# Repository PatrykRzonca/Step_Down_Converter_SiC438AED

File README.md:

# Step_Down_Converter_SiC438AED
Educational project for high current buck converters

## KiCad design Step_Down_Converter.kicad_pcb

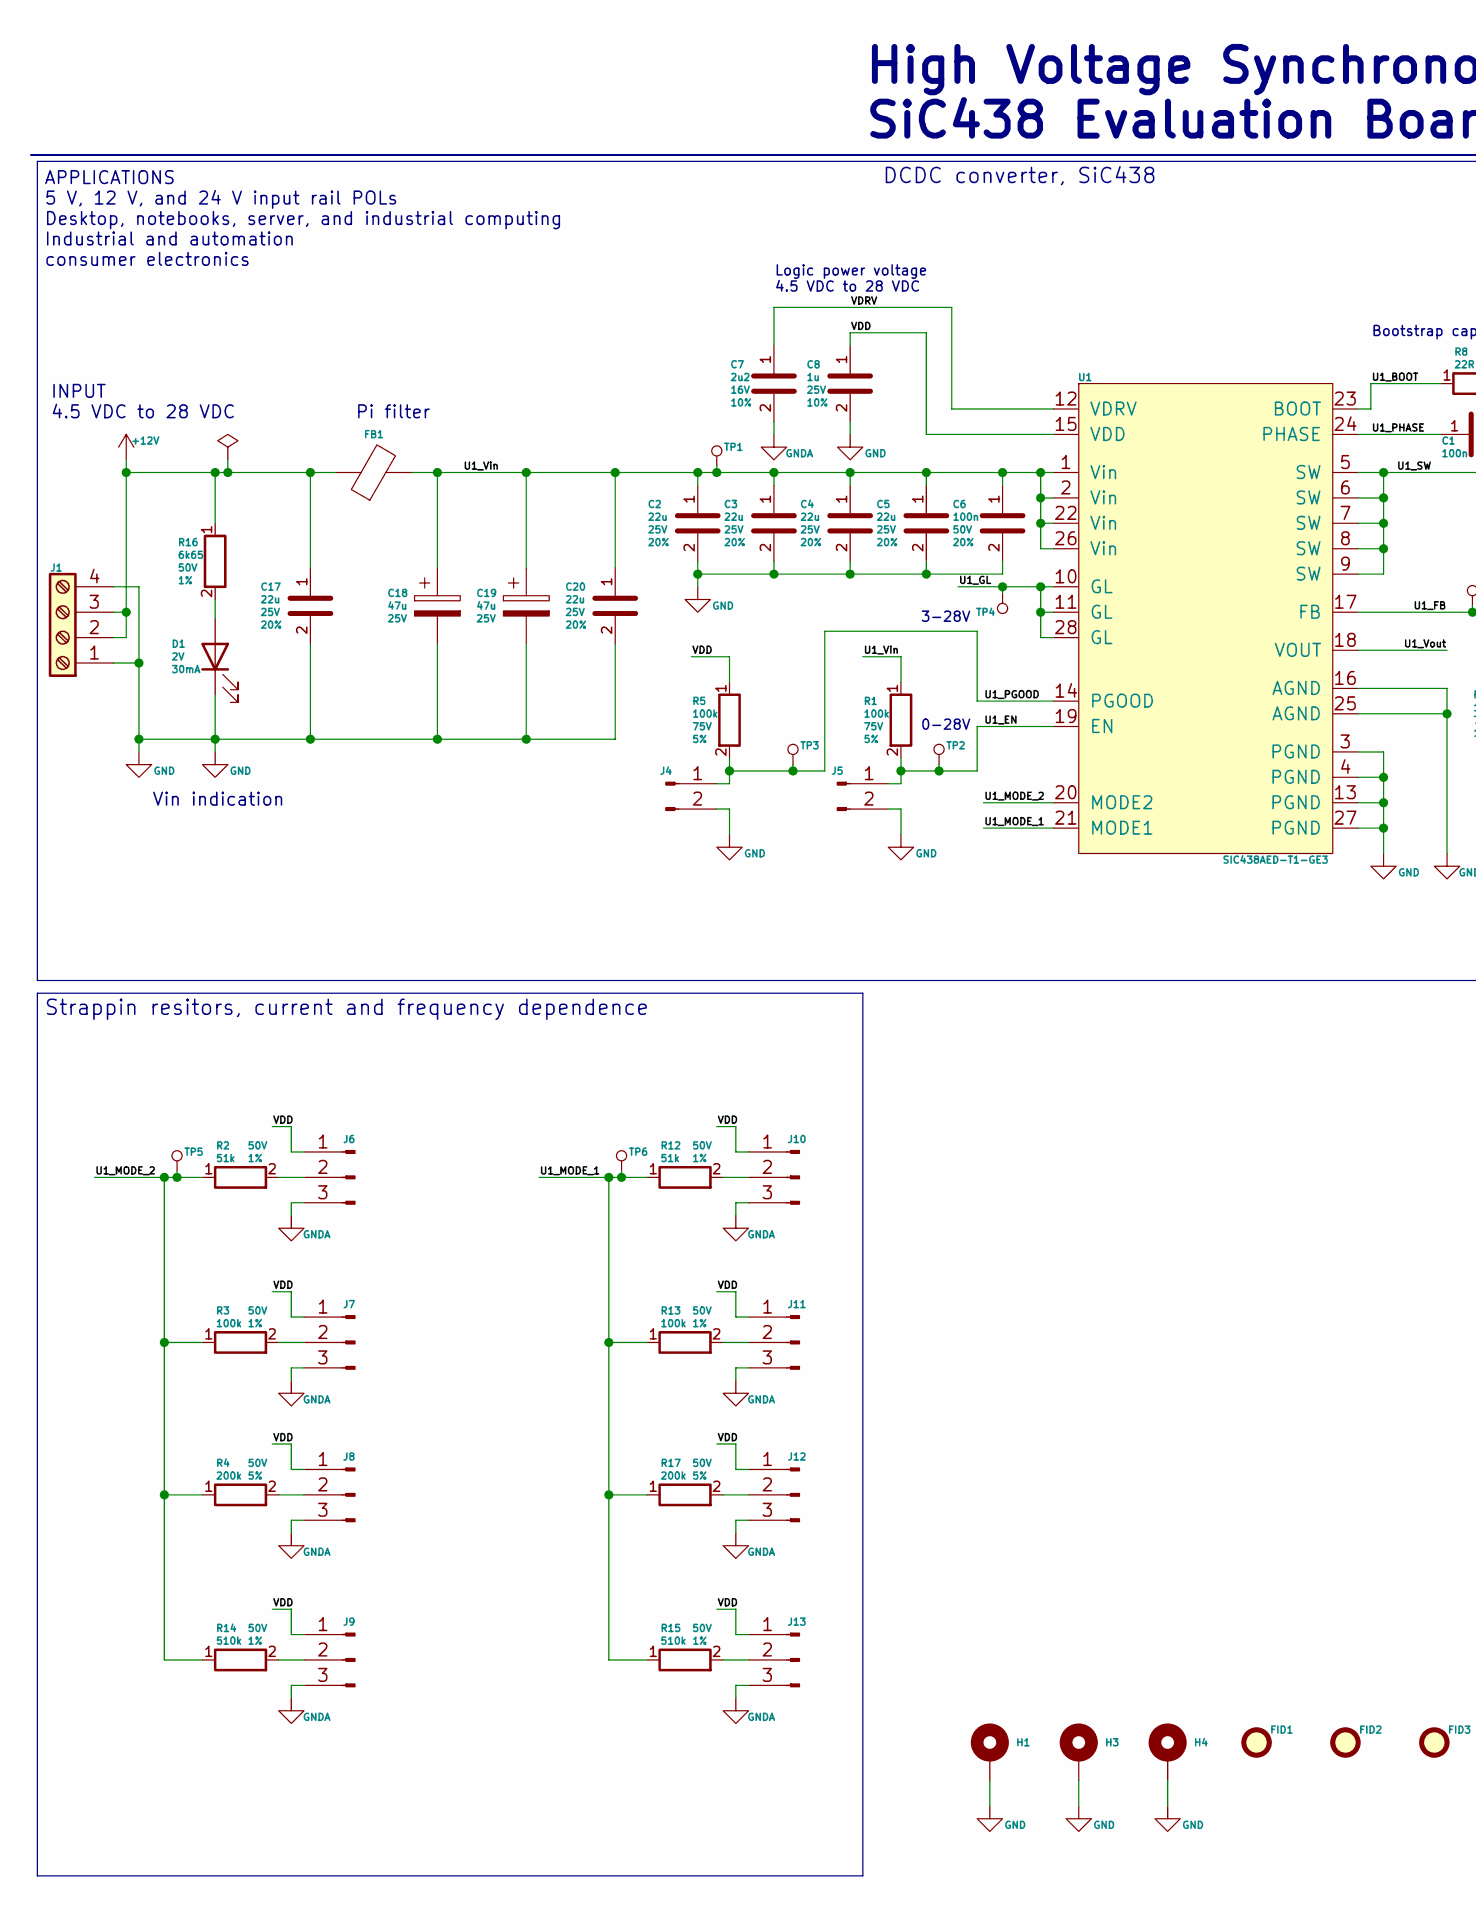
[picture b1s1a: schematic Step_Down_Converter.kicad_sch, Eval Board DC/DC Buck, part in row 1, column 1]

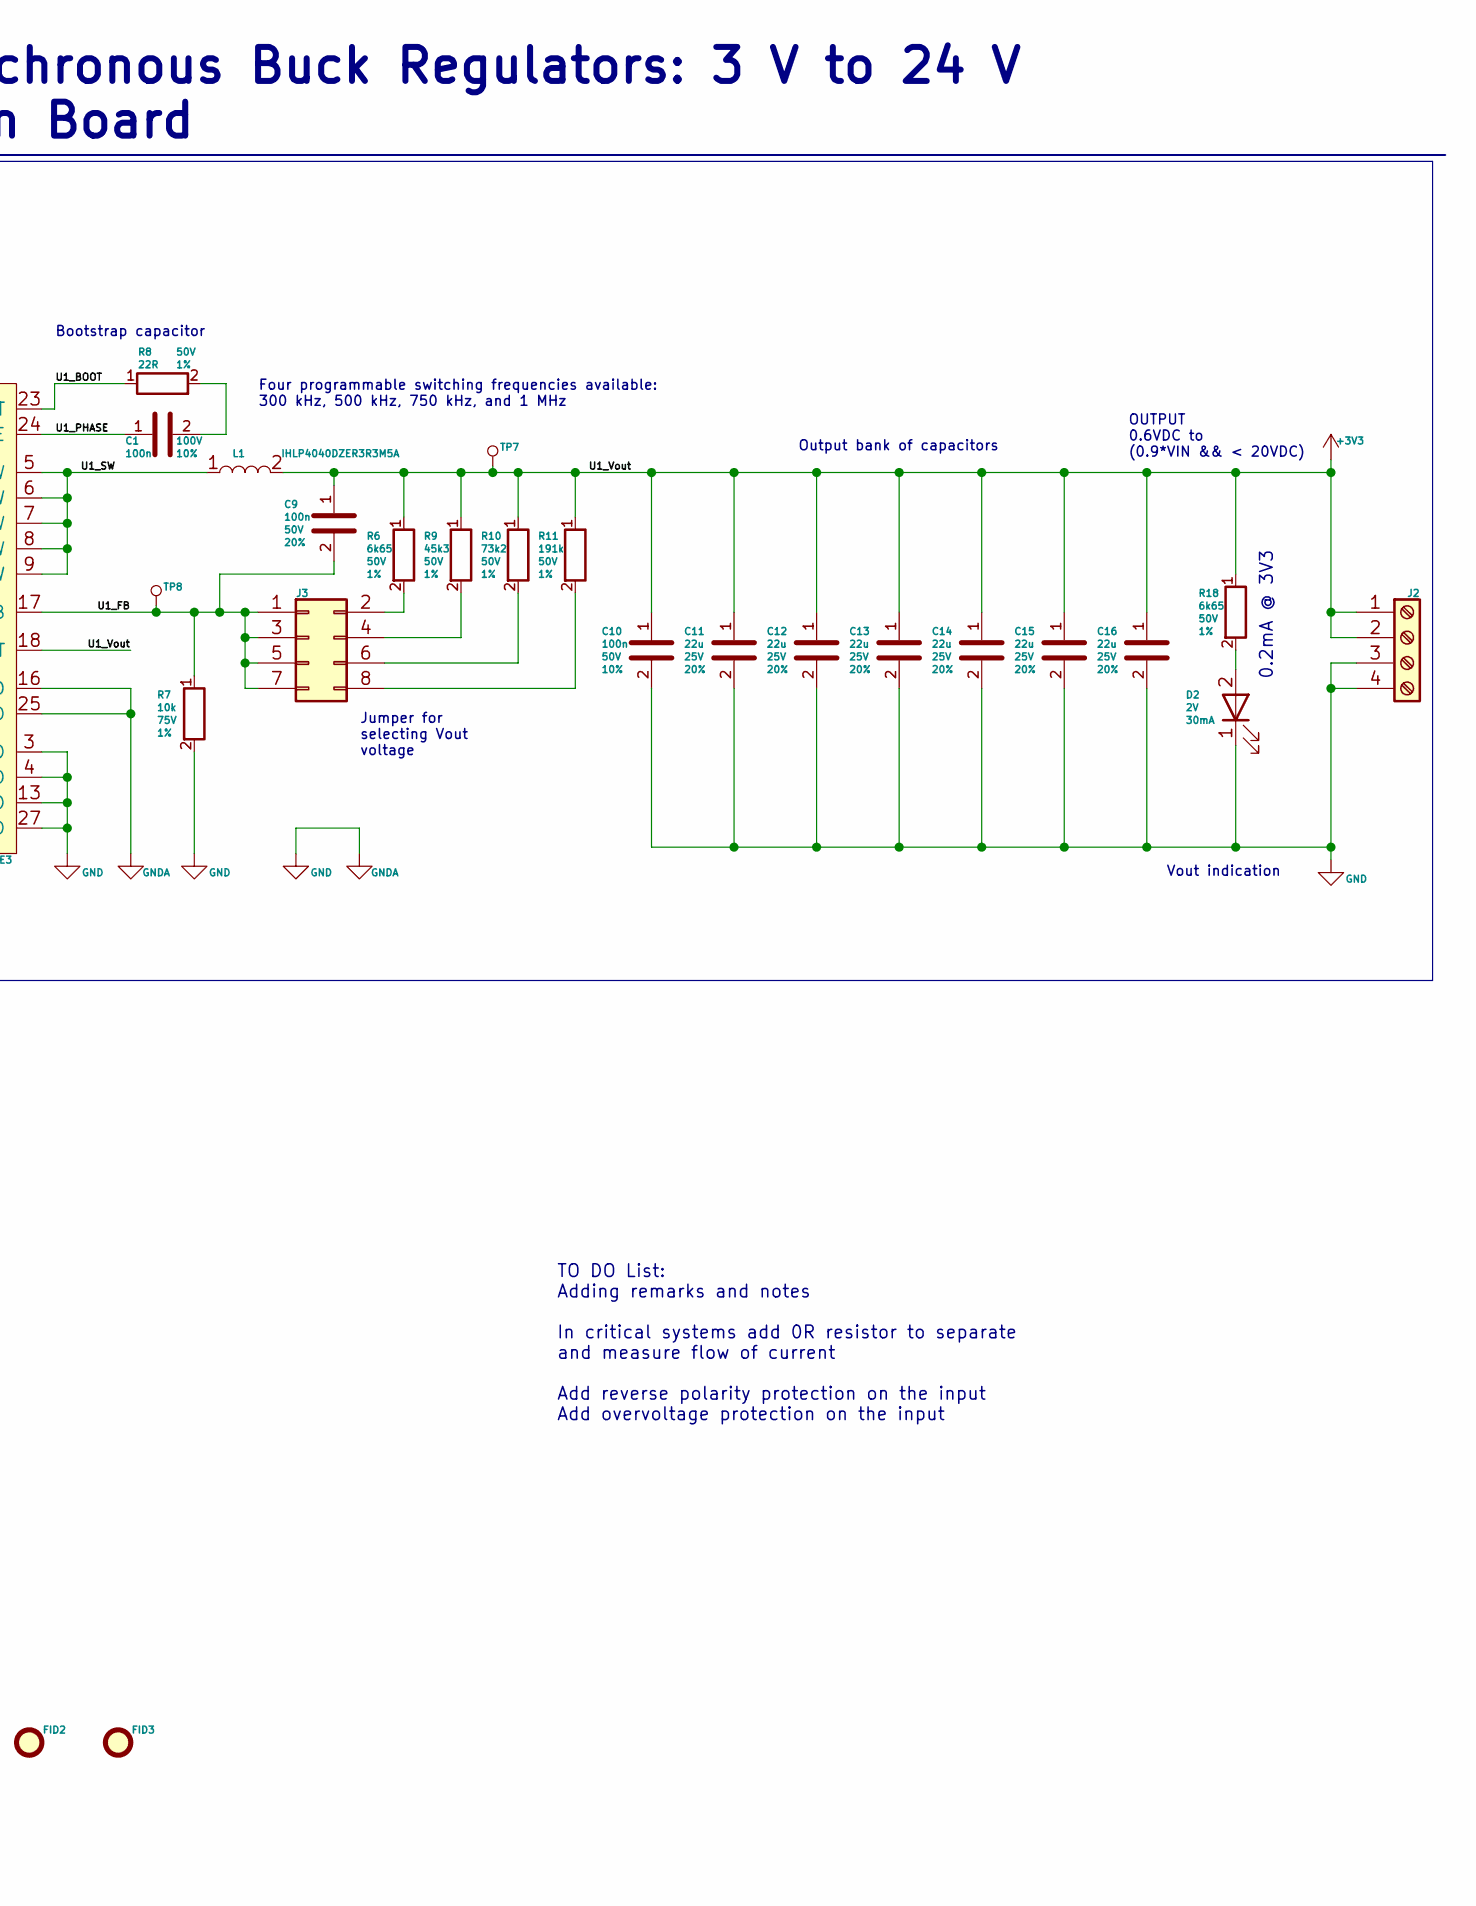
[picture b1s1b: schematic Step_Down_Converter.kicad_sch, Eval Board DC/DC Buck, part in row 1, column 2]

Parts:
C1: 100n; C_0402_1005Metric; Voltage Rating 100V; Tolerance 10%; Part Number GRM155R62A104KE14D
C2, C3, C4, C5, C11, C12, C13, C14, C15, C16, C17, C20: 22u; C_1206_3216Metric; Voltage Rating 25V; Tolerance 20%; Part Number TMK316BBJ226ML-T
C6, C9: 100n; C_0402_1005Metric; Voltage Rating 50V; Tolerance 20%; Part Number GRM155R71H104ME14D
C7: 2u2; C_0603_1608Metric; Voltage Rating 16V; Tolerance 10%; Part Number CL10A475KO8NNNC
C8: 1u; C_0603_1608Metric; Voltage Rating 25V; Tolerance 10%; Part Number CL10A105KA8NNNC
C10: 100n; C_0603_1608Metric; Voltage Rating 50V; Tolerance 10%; Part Number 06035C104KAT4A
C18, C19: 47u; CP_Elec_6.3x5.8; Voltage 25V; Tolerance 20%; Part Number UWT1E470MCL6GS
D1, D2: LED; D_0402_1005Metric; Forward Voltage 2V; Part Number 150040VS73240
FB1: FerriteBead; L_1206_3216Metric
FID1, FID2, FID3: Fiducial; Fiducial_0.5mm_Mask1mm
H1, H3, H4: MountingHole_Pad; MountingHole_3.2mm_M3_Pad
J1, J2: Screw_Terminal_01x04; CUI_TB001-500-04BE; Voltage 300V; Part Number TB001-500-04BE
J3: Conn_02x04_Odd_Even; PinHeader_2x04_P2.54mm_Vertical
J4, J5: Conn_01x02_Male; PinHeader_1x02_P2.54mm_Vertical
J6, J7, J8, J9, J10, J11, J12, J13: Conn_01x03_Male; PinHeader_1x03_P2.54mm_Vertical
L1: IHLP4040DZER3R3M5A
R1, R5: 100k; R_0603_1608Metric; Tolerance 5%; Power rating 100mW; Part Number RC0603JR-13100KL
R2, R12: 51k; R_0402_1005Metric; Tolerance 1%; Power rating 62.5mW; Part Number RC0402FR-0751KL
R3, R13: 100k; R_0402_1005Metric; Tolerance 1%; Power rating 62.5mW; Part Number RC0402FR-10100KL
R4, R17: 200k; R_0402_1005Metric; Tolerance 5%; Power rating 62.5mW; Part Number RC0402JR-13200KL
R6, R16, R18: 6k65; R_0402_1005Metric; Tolerance 1%; Power rating 62.5mW; Part Number AC0402FR-076K65L
R7: 10k; R_0603_1608Metric; Tolerance 1%; Power rating 200mW; Part Number AC0603FR-7W10KL
R8: 22R; R_0402_1005Metric; Tolerance 1%; Power rating 62.5mW; Part Number CR0402-FX-22R0GLF
R9: 45k3; R_0402_1005Metric; Tolerance 1%; Power rating 62.5mW; Part Number AF0402FR-0745K3L
R10: 73k2; R_0402_1005Metric; Tolerance 1%; Power rating 62.5mW; Part Number AC0402FR-0773K2L
R11: 191k; R_0402_1005Metric; Tolerance 1%; Power rating 62.5mW; Part Number RC0402FR-07191KL
R14, R15: 510k; R_0402_1005Metric; Tolerance 1%; Power rating 62.5mW; Part Number AC0402FR-07510KL
TP1, TP2, TP3, TP4, TP5, TP6, TP7, TP8: TestPoint; TestPoint_Pad_D1.0mm
U1: SIC438AED-T1-GE3; SIC438AED-T1-GE3_ MLP44-24

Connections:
+3V3: C9.1, C10.1, C11.1, C12.1, C13.1, C14.1, C15.1, C16.1, J2.1, J2.2, L1.2, R6.1, R9.1, R10.1, R11.1, R18.1, TP7.1, U1.18 (VOUT)
+12V: C17.1, FB1.1, J1.2, J1.3, R16.1
/U1_BOOT: R8.1, U1.23 (BOOT)
/U1_EN: J5.1, R1.2, TP2.1, U1.19 (EN)
/U1_FB: C9.2, J3.1, J3.3, J3.5, J3.7, R7.1, TP8.1, U1.17 (FB)
/U1_GL: TP4.1, U1.10 (GL), U1.11 (GL), U1.28 (GL)
/U1_MODE_1: R12.1, R13.1, R15.1, R17.1, TP6.1, U1.21 (MODE1)
/U1_MODE_2: R2.1, R3.1, R4.1, R14.1, TP5.1, U1.20 (MODE2)
/U1_PGOOD: J4.1, R5.2, TP3.1, U1.14 (PGOOD)
/U1_PHASE: C1.1, U1.24 (PHASE)
/U1_SW: L1.1, U1.5 (SW), U1.6 (SW), U1.7 (SW), U1.8 (SW), U1.9 (SW)
/U1_Vin: C2.1, C3.1, C4.1, C5.1, C6.1, C18.1, C19.1, C20.1, FB1.2, R1.1, TP1.1, U1.1 (Vin), U1.2 (Vin), U1.22 (Vin), U1.26 (Vin)
/VDD: C8.1, J6.1, J7.1, J8.1, J9.1, J10.1, J11.1, J12.1, J13.1, R5.1, U1.15 (VDD)
/VDRV: C7.1, U1.12 (VDRV)
GND: C2.2, C3.2, C4.2, C5.2, C6.2, C7.2, C8.2, C10.2, C11.2, C12.2, C13.2, C14.2, C15.2, C16.2, C17.2, C18.2, C19.2, C20.2, D1.1 (K), D2.1 (K), H1.1, H3.1, H4.1, J1.1, J1.4, J2.3, J2.4, J4.2, J5.2, J6.3, J7.3, J8.3, J9.3, J10.3, J11.3, J12.3, J13.3, R7.2, U1.3 (PGND), U1.4 (PGND), U1.13 (PGND), U1.16 (AGND), U1.25 (AGND), U1.27 (PGND)
unnamed: C1.2, R8.2
unnamed: D1.2 (A), R16.2
unnamed: D2.2 (A), R18.2
unnamed: J3.2, R6.2
unnamed: J3.4, R9.2
unnamed: J3.6, R10.2
unnamed: J3.8, R11.2
unnamed: J6.2, R2.2
unnamed: J7.2, R3.2
unnamed: J8.2, R4.2
unnamed: J9.2, R14.2
unnamed: J10.2, R12.2
unnamed: J11.2, R13.2
unnamed: J12.2, R17.2
unnamed: J13.2, R15.2

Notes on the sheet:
Output bank of capacitors
Jumper for selecting Vout voltage
Logic power voltage 4.5 VDC to 28 VDC
Vout indication
INPUT 4.5 VDC to 28 VDC
0-28V
0.2mA @ 3V3
Strappin resitors, current and frequency dependence
DCDC converter, SiC438
APPLICATIONS 5 V, 12 V, and 24 V input rail POLs Desktop, notebooks, server, and industrial computing Industrial and automation consumer electronics
Bootstrap capacitor
Vin indication
OUTPUT 0.6VDC to (0.9*VIN && < 20VDC)
3-28V
High Voltage Synchronous Buck Regulators: 3 V to 24 V SiC438 Evaluation Board
Pi filter
TO DO List: Adding remarks and notes In critical systems add 0R resistor to separate and measure flow of current Add reverse polarity protection on the input Add overvoltage protection on the input
Four programmable switching frequencies available: 300 kHz, 500 kHz, 750 kHz, and 1 MHz

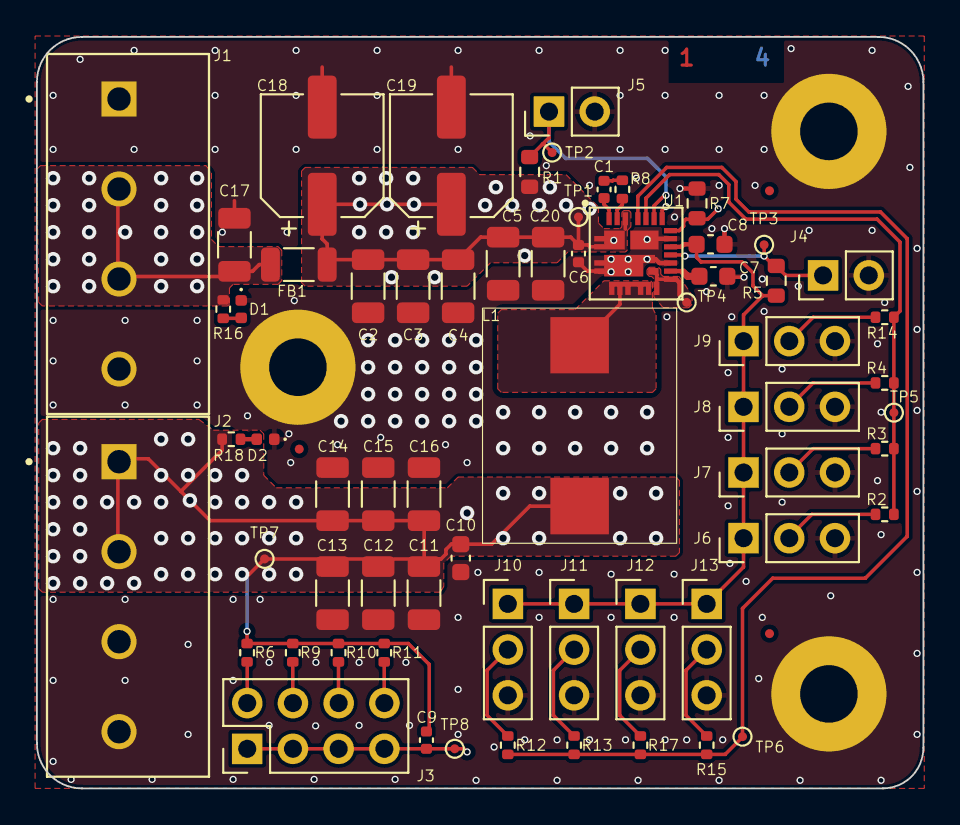
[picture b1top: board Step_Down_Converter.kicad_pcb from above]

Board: 4 copper layers, 49.2 x 41.8 mm, 70 parts (0 on the bottom side), 30 nets.
